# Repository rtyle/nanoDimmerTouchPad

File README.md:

This contains the design of a printed circuit board that can be powered by an Aeotec Nano Dimmer. It provides a touch pad that acts as an external momentary switch to the Nano Dimmer for controlling its load.

The size of the circuit board is suited for replacing the smarts in a Legrand Adorne touch switch.

The CAMOutputs can be zipped up and sent to a board fabrication shop.

Tuning ...

R1 (4k7Ω) was chosen to roughly match the LED intensity of an original Legrand Adorne touch switch.

According the the AT42QT1010 sensor datasheet (http://ww1.microchip.com/downloads/en/devicedoc/40001946a.pdf), touch sensitivity can be increased by increasing Cs, usually from 2–50nF. This (C2, 10nF) was chosen to match that on a SparkFun Capacitive Touch Breakout board (https://www.sparkfun.com/products/12041). On the bench, however, this seemed too sensitive and  was changed to 6.6nF (3 2.2nF stacked).

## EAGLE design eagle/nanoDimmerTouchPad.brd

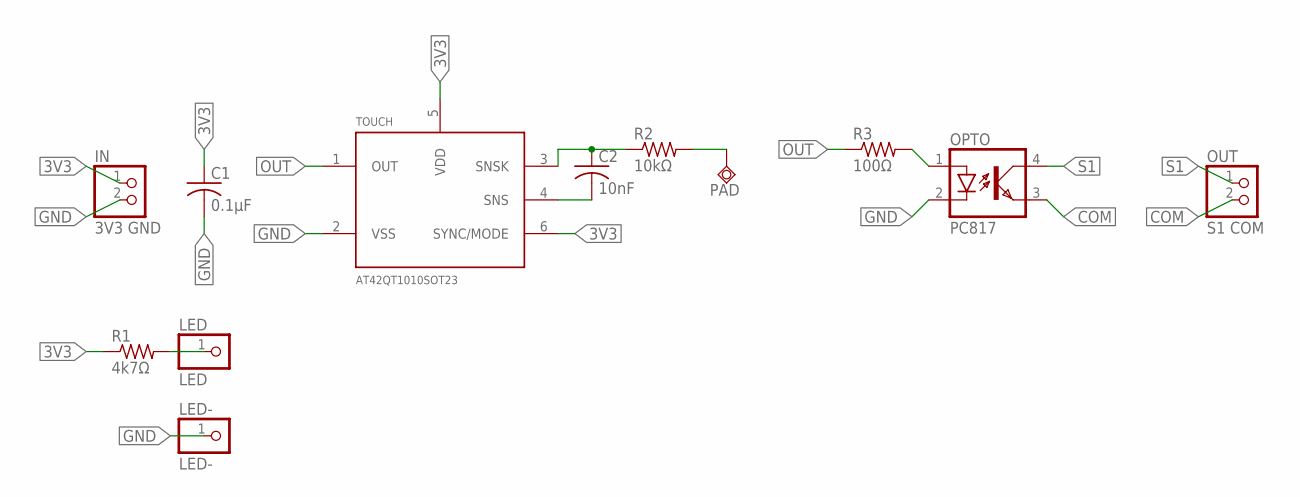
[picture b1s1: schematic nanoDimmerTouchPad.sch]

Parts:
C1: 0.1µF; C1206
C2: 10nF; C1206
IN: 3V3 GND; 1X02
LED: LED; 1X01
LED-: LED-; 1X01
OPTO: PC817; DIL04
OUT: S1 COM; 1X02
PAD: TPSQPAD1-13; P1-13
R1: 4k7Ω; R1206
R2: 10kΩ; R1206
R3: 100Ω; R1206
TOUCH: AT42QT1010SOT23; SOT23-6

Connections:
3V3: C1.1, IN.1, R1.1, TOUCH.5 (VDD), TOUCH.6 (SYNC/MODE)
COM: OPTO.3 (EMIT), OUT.2
GND: C1.2, IN.2, LED-.1, OPTO.2 (C), TOUCH.2 (VSS)
LED: LED.1, R1.2
OPTO: OPTO.1 (A), R3.2
OUT: R3.1, TOUCH.1 (OUT)
PAD: PAD.TP, R2.2
S1: OPTO.4 (COL), OUT.1
SNS: C2.2, TOUCH.4 (SNS)
SNSK: C2.1, R2.1, TOUCH.3 (SNSK)

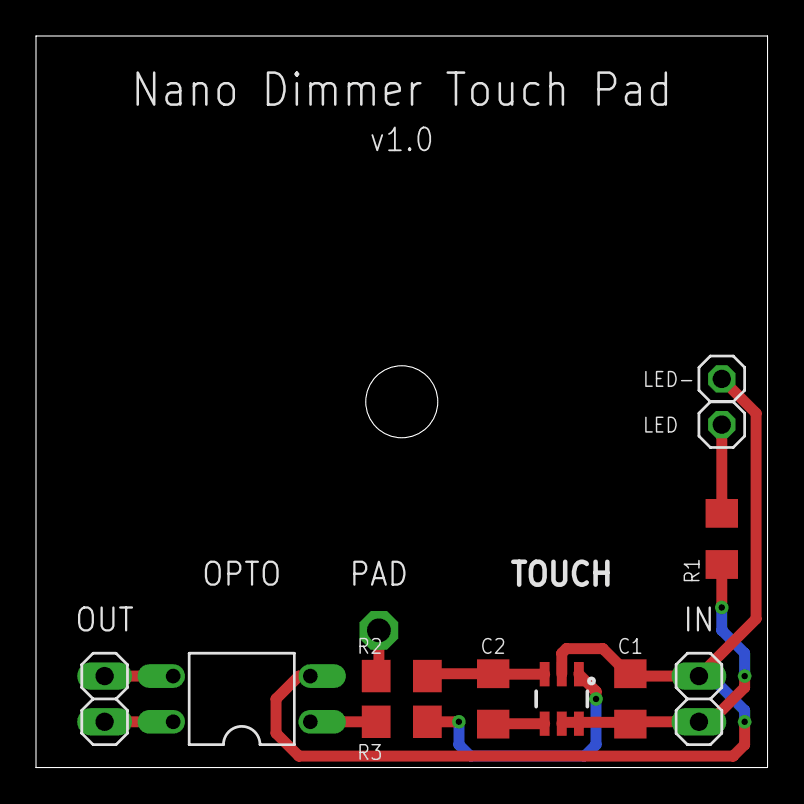
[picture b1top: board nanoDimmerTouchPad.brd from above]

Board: 2 copper layers, 40.6 x 40.6 mm, 12 parts (0 on the bottom side), 10 nets.

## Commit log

2019-07-19 initial
2019-07-19 remove executable bit
2019-07-19 Update README.md
    add fabrication and assembly instructions
2019-07-19 Update README.md
    momentary switch
2019-07-19 change indicator LED resistor from 100 to 4700 ohm to match Legrand Adorne brightness
2019-07-24 v1.0: paranoid isolation of sense circuits, no ground planes, SMD resistors and capacitors
2019-07-24 chmod a-x
2019-07-24 README.md: SMD
2019-07-24 move via totally on board
2019-08-15 README.md tuning
2019-08-15 Spelling

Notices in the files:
parts and their libraries:
SparkFun-Retired: Licensing: Creative Commons ShareAlike 4.0 International - https://creativecommons.org/licenses/by-sa/4.0
